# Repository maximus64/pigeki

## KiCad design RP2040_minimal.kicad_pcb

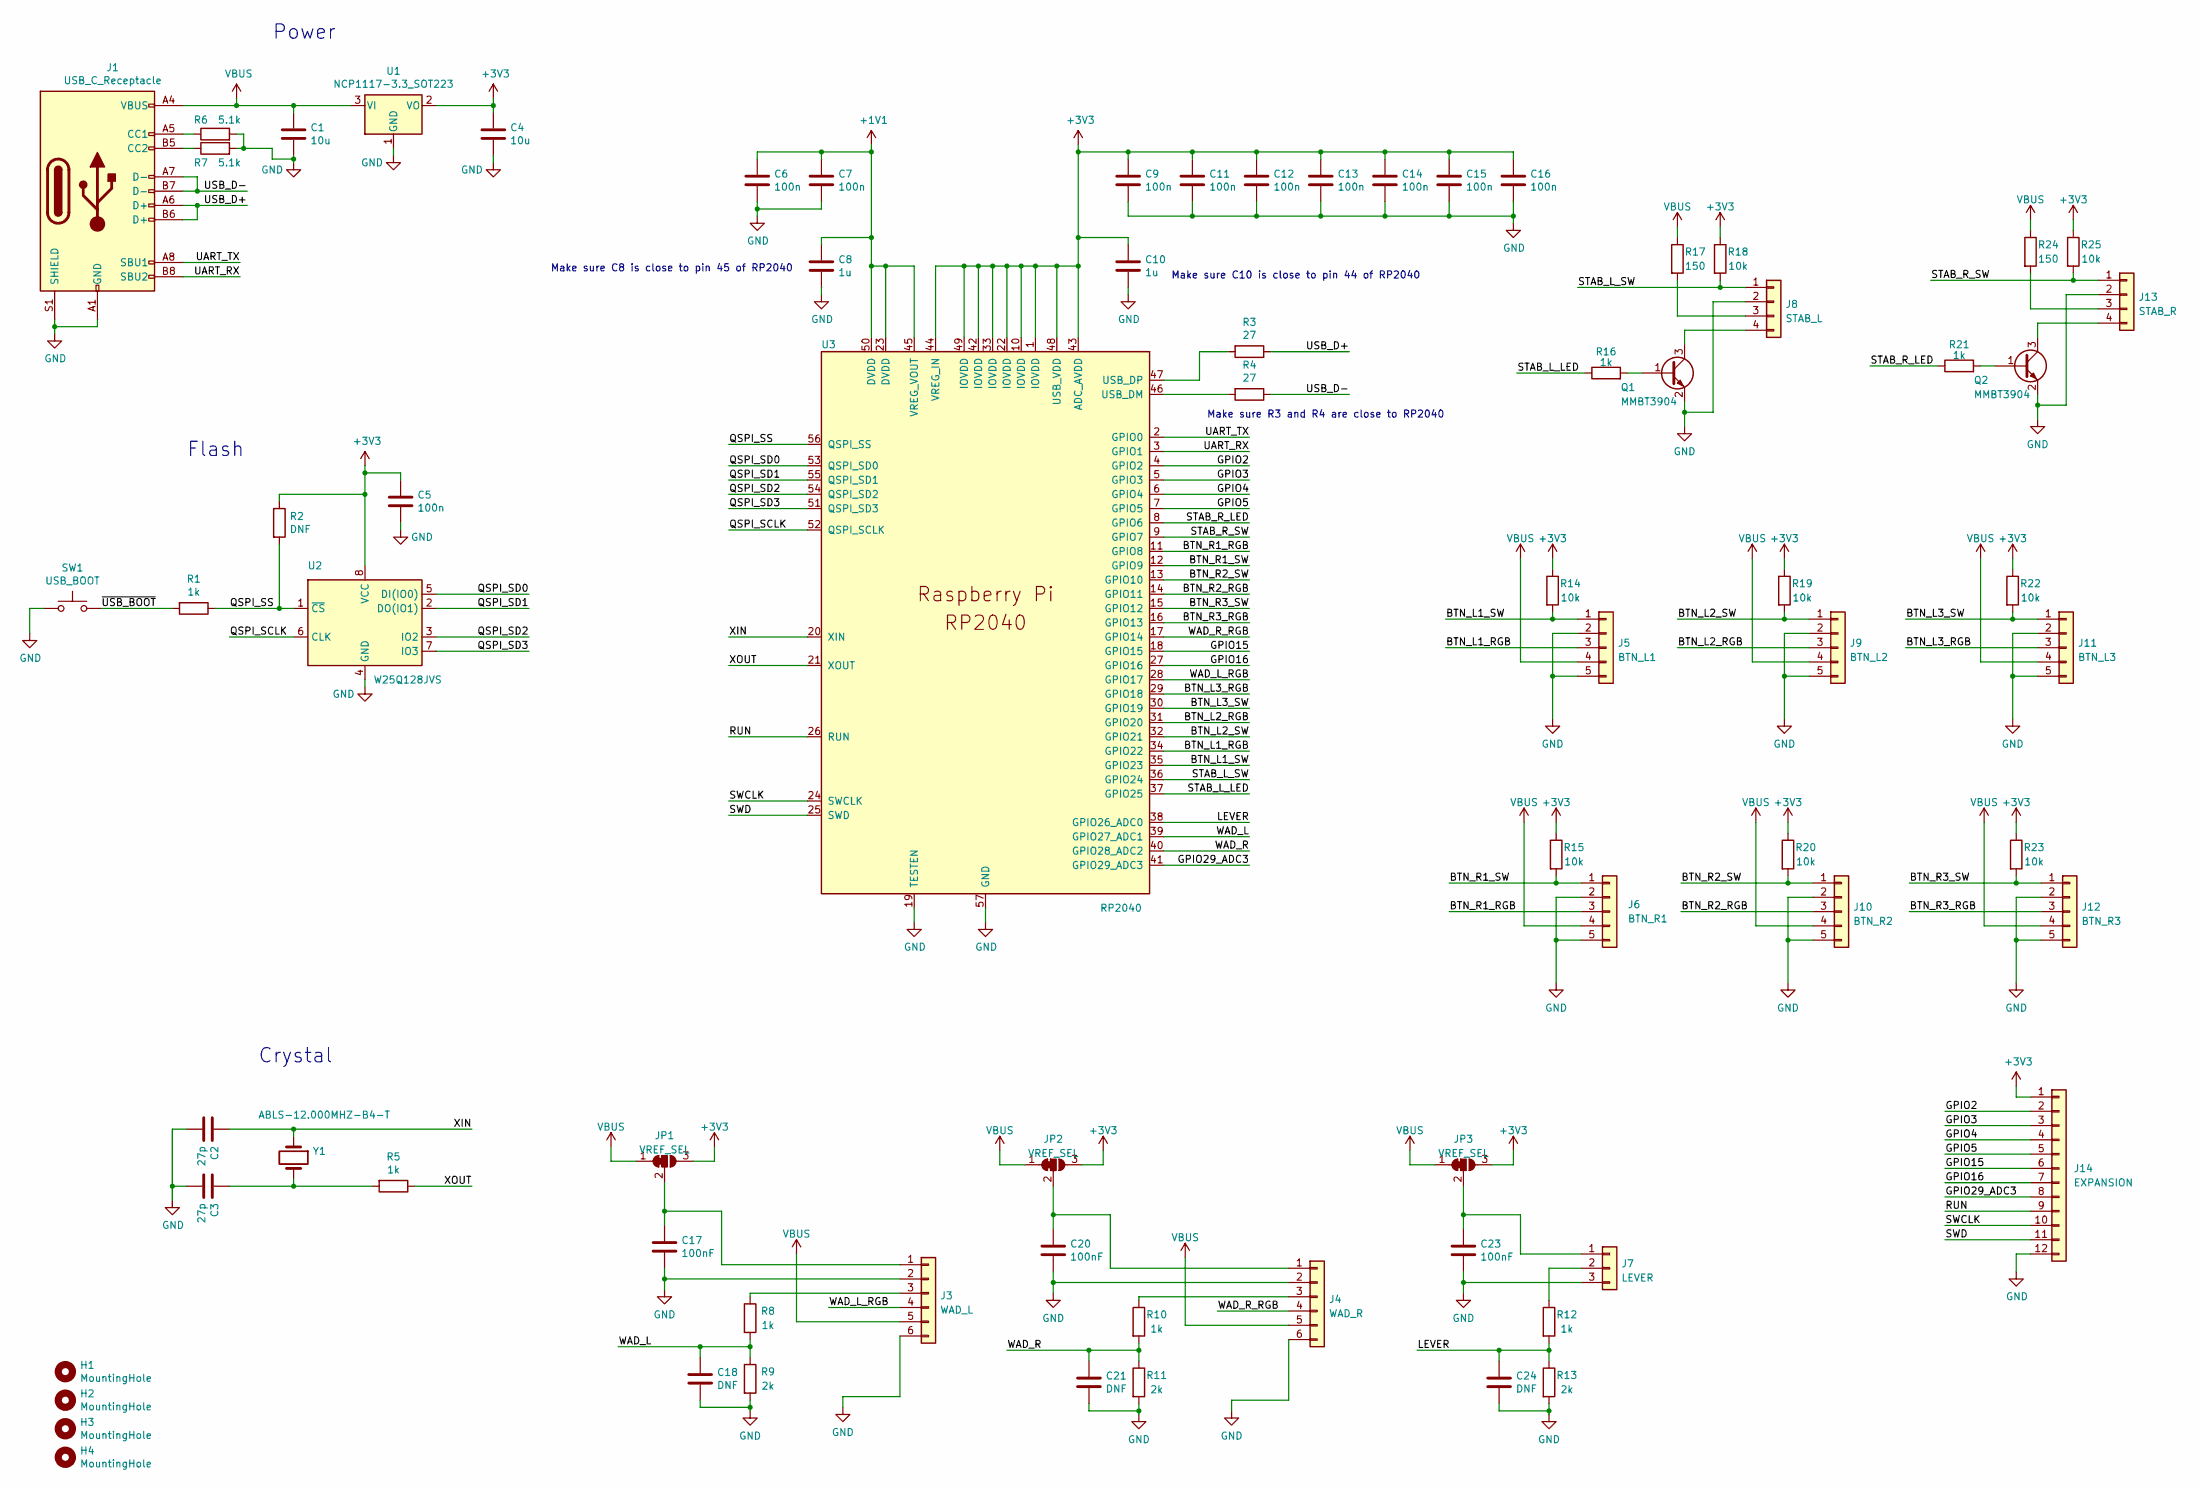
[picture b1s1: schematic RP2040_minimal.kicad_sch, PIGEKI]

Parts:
C1, C4: 10u; C_0805_2012Metric
C2, C3: 27p; C_0402_1005Metric
C5, C6, C7, C9, C11, C12, C13, C14, C15, C16: 100n; C_0402_1005Metric
C8, C10: 1u; C_0402_1005Metric
C17, C20, C23: 100nF; C_0402_1005Metric
C18, C21, C24: DNF; C_0402_1005Metric
H1, H2, H3, H4: MountingHole; MountingHole_2.7mm_M2.5
J1: USB_C_Receptacle; USB_C_Receptacle_Palconn_UTC16-G
J3: WAD_L; JST_XH_B6B-XH-A_1x06_P2.50mm_Vertical
J4: WAD_R; JST_XH_B6B-XH-A_1x06_P2.50mm_Vertical
J5: BTN_L1; JST_XH_B5B-XH-A_1x05_P2.50mm_Vertical
J6: BTN_R1; JST_XH_B5B-XH-A_1x05_P2.50mm_Vertical
J7: LEVER; JST_XH_B3B-XH-A_1x03_P2.50mm_Vertical
J8: STAB_L; JST_XH_B4B-XH-A_1x04_P2.50mm_Vertical
J9: BTN_L2; JST_XH_B5B-XH-A_1x05_P2.50mm_Vertical
J10: BTN_R2; JST_XH_B5B-XH-A_1x05_P2.50mm_Vertical
J11: BTN_L3; JST_XH_B5B-XH-A_1x05_P2.50mm_Vertical
J12: BTN_R3; JST_XH_B5B-XH-A_1x05_P2.50mm_Vertical
J13: STAB_R; JST_XH_B4B-XH-A_1x04_P2.50mm_Vertical
J14: EXPANSION; PinHeader_1x12_P2.54mm_Vertical
JP1, JP2, JP3: VREF_SEL; SolderJumper-3_P1.3mm_Bridged12_RoundedPad1.0x1.5mm_NumberL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
Q1, Q2: MMBT3904; SOT-23
R1, R5, R8, R10, R12, R16, R21: 1k; C_0402_1005Metric
R2: DNF; C_0402_1005Metric
R3, R4: 27; C_0402_1005Metric
R6, R7: 5.1k; R_0402_1005Metric
R9, R11, R13: 2k; C_0402_1005Metric
R14, R15, R18, R19, R20, R22, R23, R25: 10k; C_0402_1005Metric
R17, R24: 150; C_0402_1005Metric
SW1: USB_BOOT; SW_Push_1P1T_NO_CK_KMR2
U1: NCP1117-3.3_SOT223; SOT-223-3_TabPin2
U2: W25Q128JVS; SOIC-8_5.23x5.23mm_P1.27mm
U3: RP2040; RP2040-QFN-56
Y1: ABLS-12.000MHZ-B4-T; Crystal_SMD_HC49-US

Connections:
+1V1: C6.1, C7.1, C8.1, U3.23 (DVDD), U3.45 (VREG_VOUT), U3.50 (DVDD)
+3V3: C4.1, C5.1, C9.1, C10.1, C11.1, C12.1, C13.1, C14.1, C15.1, C16.1, J14.1, JP1.3 (B), JP2.3 (B), JP3.3 (B), R2.1, R14.1, R15.1, R18.1, R19.1, R20.1, R22.1, R23.1, R25.1, U1.2 (VO), U2.8 (VCC), U3.1 (IOVDD), U3.10 (IOVDD), U3.22 (IOVDD), U3.33 (IOVDD), U3.42 (IOVDD), U3.43 (ADC_AVDD), U3.44 (VREG_IN), U3.48 (USB_VDD), U3.49 (IOVDD)
/BTN_L1_RGB: J5.3, U3.34 (GPIO22)
/BTN_L1_SW: J5.1, R14.2, U3.35 (GPIO23)
/BTN_L2_RGB: J9.3, U3.31 (GPIO20)
/BTN_L2_SW: J9.1, R19.2, U3.32 (GPIO21)
/BTN_L3_RGB: J11.3, U3.29 (GPIO18)
/BTN_L3_SW: J11.1, R22.2, U3.30 (GPIO19)
/BTN_R1_RGB: J6.3, U3.11 (GPIO8)
/BTN_R1_SW: J6.1, R15.2, U3.12 (GPIO9)
/BTN_R2_RGB: J10.3, U3.14 (GPIO11)
/BTN_R2_SW: J10.1, R20.2, U3.13 (GPIO10)
/BTN_R3_RGB: J12.3, U3.16 (GPIO13)
/BTN_R3_SW: J12.1, R23.2, U3.15 (GPIO12)
/GPIO2: J14.2, U3.4 (GPIO2)
/GPIO3: J14.3, U3.5 (GPIO3)
/GPIO4: J14.4, U3.6 (GPIO4)
/GPIO5: J14.5, U3.7 (GPIO5)
/GPIO15: J14.6, U3.18 (GPIO15)
/GPIO16: J14.7, U3.27 (GPIO16)
/GPIO29_ADC3: J14.8, U3.41 (GPIO29_ADC3)
/LEVER: C24.1, R12.2, R13.1, U3.38 (GPIO26_ADC0)
/QSPI_SCLK: U2.6 (CLK), U3.52 (QSPI_SCLK)
/QSPI_SD0: U2.5 (DI(IO0)), U3.53 (QSPI_SD0)
/QSPI_SD1: U2.2 (DO(IO1)), U3.55 (QSPI_SD1)
/QSPI_SD2: U2.3 (IO2), U3.54 (QSPI_SD2)
/QSPI_SD3: U2.7 (IO3), U3.51 (QSPI_SD3)
/QSPI_SS: R1.1, R2.2, U2.1 (~CS), U3.56 (QSPI_SS)
/RUN: J14.9, U3.26 (RUN)
/STAB_L_LED: R16.1, U3.37 (GPIO25)
/STAB_L_SW: J8.1, R18.2, U3.36 (GPIO24)
/STAB_R_LED: R21.1, U3.8 (GPIO6)
/STAB_R_SW: J13.1, R25.2, U3.9 (GPIO7)
/SWCLK: J14.10, U3.24 (SWCLK)
/SWD: J14.11, U3.25 (SWD)
/UART_RX: J1.B8 (SBU2), U3.3 (GPIO1)
/UART_TX: J1.A8 (SBU1), U3.2 (GPIO0)
/USB_D+: J1.A6 (D+), J1.B6 (D+), R3.1
/USB_D-: J1.A7 (D-), J1.B7 (D-), R4.1
/WAD_L: C18.1, R8.2, R9.1, U3.39 (GPIO27_ADC1)
/WAD_L_RGB: J3.4, U3.28 (GPIO17)
/WAD_R: C21.1, R10.2, R11.1, U3.40 (GPIO28_ADC2)
/WAD_R_RGB: J4.4, U3.17 (GPIO14)
/XIN: C2.1, U3.20 (XIN), Y1.1
/XOUT: R5.1, U3.21 (XOUT)
/~USB_BOOT: R1.2, SW1.2
GND: C1.2, C2.2, C3.2, C4.2, C5.2, C6.2, C7.2, C8.2, C9.2, C10.2, C11.2, C12.2, C13.2, C14.2, C15.2, C16.2, C17.2, C18.2, C20.2, C21.2, C23.2, C24.2, J1.A1 (GND), J1.A12 (GND), J1.B1 (GND), J1.B12 (GND), J1.S1 (SHIELD), J3.2, J3.6, J4.2, J4.6, J5.2, J5.5, J6.2, J6.5, J7.3, J8.2, J9.2, J9.5, J10.2, J10.5, J11.2, J11.5, J12.2, J12.5, J13.2, J14.12, Q1.2 (E), Q2.2 (E), R6.2, R7.2, R9.2, R11.2, R13.2, SW1.1, U1.1 (GND), U2.4 (GND), U3.19 (TESTEN), U3.57 (GND)
unnamed: C3.1, R5.2, Y1.2
unnamed: C17.1, J3.1, JP1.2 (C)
unnamed: C20.1, J4.1, JP2.2 (C)
unnamed: C23.1, J7.1, JP3.2 (C)
unnamed: J1.A5 (CC1), R6.1
unnamed: J1.B5 (CC2), R7.1
unnamed: J3.3, R8.1
unnamed: J4.3, R10.1
unnamed: J7.2, R12.1
unnamed: J8.3, R17.2
unnamed: J8.4, Q1.3 (C)
unnamed: J13.3, R24.2
unnamed: J13.4, Q2.3 (C)
unnamed: Q1.1 (B), R16.2
unnamed: Q2.1 (B), R21.2
unnamed: R3.2, U3.47 (USB_DP)
unnamed: R4.2, U3.46 (USB_DM)
VBUS: C1.1, J1.A4 (VBUS), J1.A9 (VBUS), J1.B4 (VBUS), J1.B9 (VBUS), J3.5, J4.5, J5.4, J6.4, J9.4, J10.4, J11.4, J12.4, JP1.1 (A), JP2.1 (A), JP3.1 (A), R17.1, R24.1, U1.3 (VI)

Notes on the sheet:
Power
Flash
Make sure C10 is close to pin 44 of RP2040
Crystal
Make sure C8 is close to pin 45 of RP2040
Make sure R3 and R4 are close to RP2040

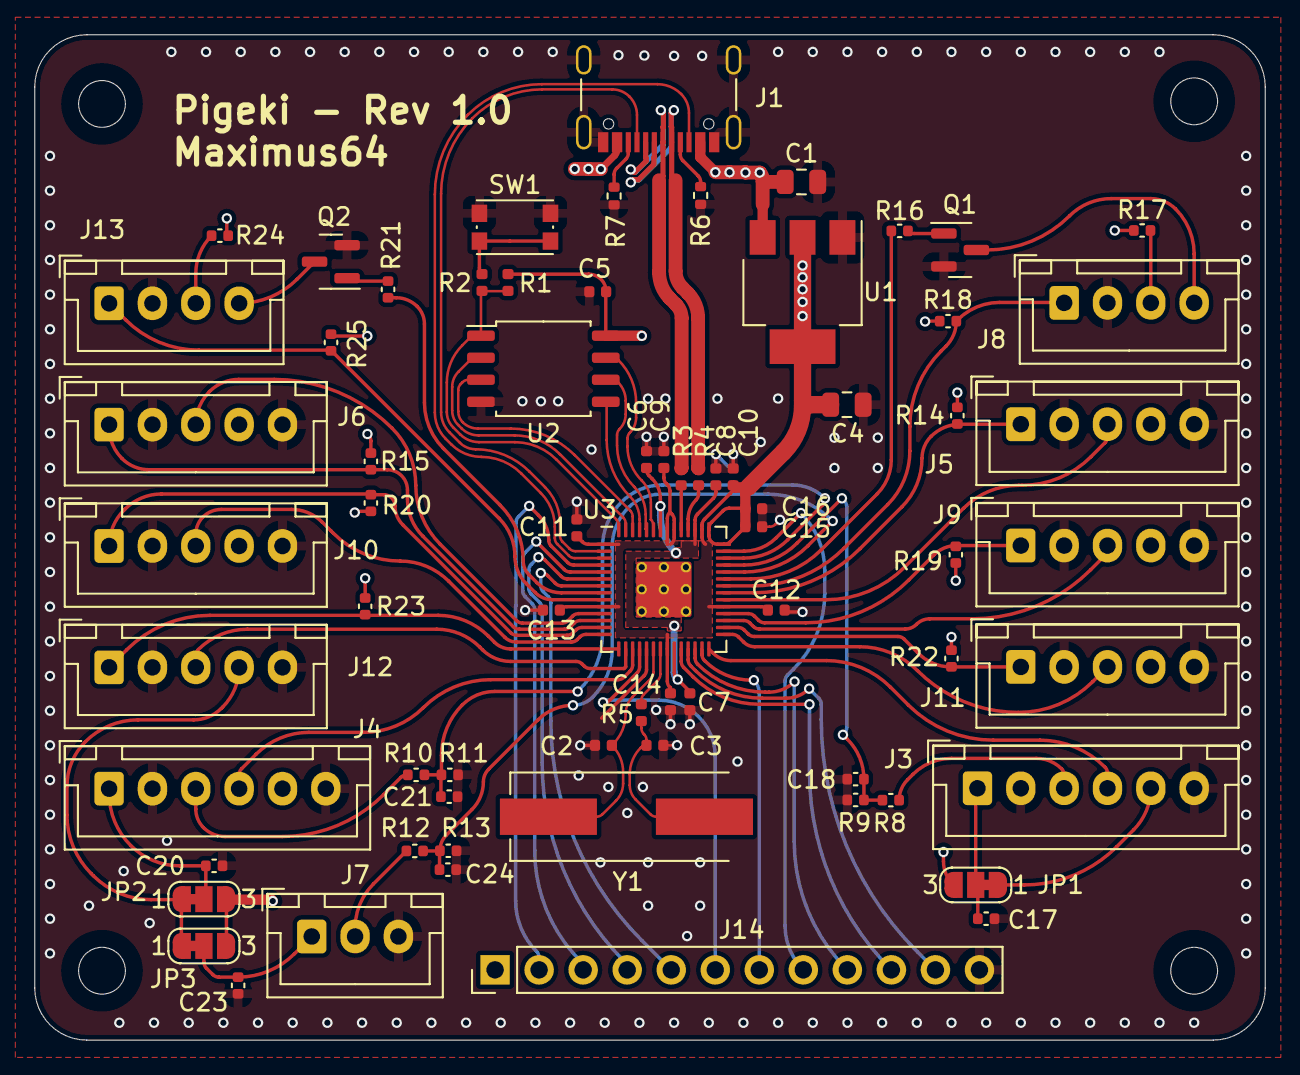
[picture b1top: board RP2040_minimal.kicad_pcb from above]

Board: 2 copper layers, 71.0 x 58.0 mm, 74 parts (0 on the bottom side), 65 nets.

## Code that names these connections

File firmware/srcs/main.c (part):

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#define BIT(x) (1UL << (x))

/* GPIO pins definition */
#define BTN_L1_RGB_GPIO 22
#define BTN_L2_RGB_GPIO 20
#define BTN_L3_RGB_GPIO 18
#define WAD_L_RGB_GPIO 17

#define BTN_R1_RGB_GPIO 8
#define BTN_R2_RGB_GPIO 11
#define BTN_R3_RGB_GPIO 13
#define WAD_R_RGB_GPIO 14

#define BTN_STAB_L_LED_GPIO 25
#define BTN_STAB_R_LED_GPIO 6

#define BTN_L1_SW_GPIO 23
#define BTN_L2_SW_GPIO 21
#define BTN_L3_SW_GPIO 19
#define BTN_STAB_L_SW_GPIO 24

#define BTN_R1_SW_GPIO 9
#define BTN_R2_SW_GPIO 10
#define BTN_R3_SW_GPIO 12
#define BTN_STAB_R_SW_GPIO 7

#define LEVER_ADC_GPIO 26
#define WAD_L_ADC_GPIO 27
#define WAD_R_ADC_GPIO 28
#define VBUS_ADC_GPIO 29 /* Measure VBUS so we can correct lever input */


#define RGB_BIT_MASK ( BIT(BTN_L1_RGB_GPIO) | \
                       BIT(BTN_L2_RGB_GPIO) | \
                       BIT(BTN_L3_RGB_GPIO) | \
                       BIT(WAD_L_RGB_GPIO)  | \
                       BIT(BTN_R1_RGB_GPIO) | \
                       BIT(BTN_R2_RGB_GPIO) | \
                       BIT(BTN_R3_RGB_GPIO) | \
                       BIT(WAD_R_RGB_GPIO) )

/* Longest LED chain length - WAD have 9x3 in parallel */
#define LED_CHAIN_LENGTH 9
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#define WAD_R_RGB_IDX  7

static const uint8_t rgb_gpios[8] = {
    BTN_L1_RGB_GPIO,
    BTN_L2_RGB_GPIO,
    BTN_L3_RGB_GPIO,
    WAD_L_RGB_GPIO,
    BTN_R1_RGB_GPIO,
    BTN_R2_RGB_GPIO,
    BTN_R3_RGB_GPIO,
    WAD_R_RGB_GPIO
};

typedef union {
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static spin_lock_t *rgb_spin_lock;

static const uint8_t sw_gpios[] = {
    BTN_L1_SW_GPIO,
    BTN_L2_SW_GPIO,
    BTN_L3_SW_GPIO,
    BTN_STAB_L_SW_GPIO,
    BTN_R1_SW_GPIO,
    BTN_R2_SW_GPIO,
    BTN_R3_SW_GPIO,
    BTN_STAB_R_SW_GPIO,
};

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    start_ms += interval_ms;

    if (tud_hid_ready()) {
        report.buttons = button_get(BTN_L1_SW_GPIO) |
                         (button_get(BTN_L2_SW_GPIO) << 1) |
                         (button_get(BTN_L3_SW_GPIO) << 2) |
                         (button_get(BTN_STAB_L_SW_GPIO) << 3) |
                         (button_get(BTN_R1_SW_GPIO) << 4) |
                         (button_get(BTN_R2_SW_GPIO) << 5) |
                         (button_get(BTN_R3_SW_GPIO) << 6) |
                         (button_get(BTN_STAB_R_SW_GPIO) << 7);
        report.x = lever_pos;
        report.y = wad_l_pos;
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
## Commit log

2023-03-07 add pi pico sdk
2023-03-07 hello world
2023-03-08 implement asm code to drive multiple WS2812B RGB LED
2023-03-09 put rgb_shift() into RAM to make timming more stable. tunned RGB timming
2023-03-09 add mutex guard when set LED color and drop to USB boot after 7s for now
2023-03-09 use spinlock instead of mutex for rgb color
2023-03-09 remove obsolete schematic
2023-03-10 implement button debouncer
2023-03-10 add copyright
2023-03-10 bring up PWM to drive the stab button LED
2023-03-10 bring up ADC
2023-03-11 change ADC to 8 bits as lower bits are noise anyway
2023-03-11 USB HID Gamepad bring up
2023-03-11 lower GPIO drive strength to reduce EMI
2023-03-11 add scaler + filter for analog input
2023-03-15 seperate out WAD calibration value as they don't match
2023-03-15 limit WAD LED power
2023-03-15 recal lever
2023-03-15 add lever voltage drop correction
2023-03-15 implement set led HID command, remove debug code
2023-03-15 add start up glow LED animation

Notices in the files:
firmware/srcs/main.c:
Copyright (c) 2023 Khoa Hoang <admin@khoahoang.com>
